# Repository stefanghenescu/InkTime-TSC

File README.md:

# InkTime TSC

## Block Diagram

---

## Bill of Materials (BOM)

| Name | Component Type | Package | Part Number / Value | Qty | JLCPCB Part Link | Datasheet Link |
| :--- | :--- | :--- | :--- | :--- | :--- | :--- |
| **U1** | MCU | AQFN-74 | NRF52840 | 1 | [View Part](https://jlcpcb.com/partdetail/NordicSemicon-NRF52840_QIAAR/C190794) | [View Datasheet](https://resources.ampheo.com/static/datasheets/nordic-semiconductor/nrf52840-qiaa-r-rev2.pdf) |
| **IC1** | LiPo Charger | DSBGA-8 | BQ25180YBGR | 1 | [View Part](https://jlcpcb.com/partdetail/TexasInstruments-BQ25180YBGR/C3682423) | [View Datasheet](https://www.ti.com/lit/ds/symlink/bq25180.pdf?ts=1776583277258) |
| **IC2** | Haptic Driver | DSBGA-9 | DRV2605YZFR | 1 | [View Part](https://jlcpcb.com/partdetail/TexasInstruments-DRV2605YZFR/C81079) | [View Datasheet](https://www.ti.com/lit/ds/symlink/drv2605.pdf) |
| **IC3** | IMU / Accelerometer | LGA-12 | BMA423 | 1 | [View Part](https://jlcpcb.com/partdetail/BoschSensortec-BMA421/C5242966) | [View Datasheet](https://files.pine64.org/doc/datasheet/pinetime/BST-BMA421-FL000.pdf) |
| **IC9** | DC/DC Converter | 15-WL-CSP | RT6160AWSC | 1 | [View Part](https://jlcpcb.com/partdetail/RichtekTech-RT6160AWSC/C7065276) | [View Datasheet](https://www.lcsc.com/datasheet/C7065276.pdf?spm=wm.sxq.inf.ggs___wm.ssy.bg.0.xh&lcsc_vid=RVILV1QAFgMLXlRXRFQPBVVeFgVaXwJQTwdfAlJXFAUxVlNRQVReUlFfQVZbUTsOAxUeFF5JWBYZEEoKFBINSQcJGk4dAgUUFAk%3D) |
| **U3** | Fuel Gauge | TDFN-8 | MAX17048G+T10 | 1 | [View Part](https://jlcpcb.com/partdetail/2777647-MAX17048GT10/C2682616) | [View Datasheet](https://www.analog.com/media/en/technical-documentation/data-sheets/max17048-max17049.pdf) |
| **ANT1** | Chip Antenna | ANTC3216 | 2450AT18B100E | 1 | [View Part](https://jlcpcb.com/partdetail/JohansonDielectrics-2450AT18B100E/C2917717) | [View Datasheet](https://www.johansontechnology.com/docs/1187/2450AT18B100_X8XXogU.pdf) |
| **J1** | FPC Connector | 5034802400 | 503480-2400 | 1 | [View Part](https://jlcpcb.com/partdetail/MOLEX-5034802400/C122434) | [View Datasheet](https://www.mouser.com/datasheet/2/276/2/5034802400_FFC_FPC_CONNECTORS-1112921.pdf?srsltid=AfmBOoqeIvrMEurBUIMiLpCQbdFw00xQXV8qCybaZ2IhZAIdW5Bf1d4q) |
| **J2** | Debug Connector | TC2030IDC | TC2030-IDC | 1 | - | [View Datasheet](https://www.tag-connect.com/wp-content/uploads/bsk-pdf-manager/2019/12/TC2030-IDC-Datasheet-Rev-B.pdf) |
| **J4** | USB-C Connector | KH-TYPE-C-16P | KH-TYPE-C-16P | 1 | [View Part](https://jlcpcb.com/partdetail/Shenzhen_KinghelmElec-KH_TYPE_C16P/C709357) | [View Datasheet](https://www.lcsc.com/datasheet/C709357.pdf) |
| **Q1** | P-Channel MOSFET | SOT23-3 | DMG2305UX-7 | 1 | [View Part](https://jlcpcb.com/partdetail/DiodesIncorporated-DMG2305UX7/C150470) | [View Datasheet](https://www.lcsc.com/datasheet/C150470.pdf?spm=wm.sxq.inf.ggs___wm.ssy.bg.0.xh&lcsc_vid=RVILV1QAFgMLXlRXRFQPBVVeFgVaXwJQTwdfAlJXFAUxVlNRQVReUVxRQFhXUzsOAxUeFF5JWBYZEEoKFBINSQcJGk4dAgUUFAk%3D) |
| **Q3** | N-Channel MOSFET | SC-70 / SOT-323 | SI1308EDL-T1-GE3 | 1 | [View Part](https://jlcpcb.com/partdetail/VishayIntertech-SI1308EDL_T1GE3/C469327) | [View Datasheet](https://www.lcsc.com/datasheet/C469327.pdf?spm=wm.sxq.inf.ggs___wm.ssy.bg.0.xh&lcsc_vid=RVILV1QAFgMLXlRXRFQPBVVeFgVaXwJQTwdfAlJXFAUxVlNRQVReUVBWQ1VdVDsOAxUeFF5JWBYZEEoKFBINSQcJGk4eFQsCAgIaSgADAwAHC0slQFFYUlZRQU8GEwkK) |
| **D2, D4, D5** | Schottky Diode | SOD-123 | MBR0530 | 3 | [View Part](https://jlcpcb.com/partdetail/78464-MBR0530/C77336) | [View Datasheet](https://www.onsemi.com/pdf/datasheet/mbr0530-d.pdf) |
| **D3** | ESD Protection | SOT23-6 | USBLC6-2SC6Y | 1 | [View Part](https://jlcpcb.com/partdetail/STMicroelectronics-USBLC62SC6Y/C2969755) | [View Datasheet](https://www.st.com/resource/en/datasheet/usblc6-2sc6y.pdf) |
| **SW_DN, SW_ENT, SW_UP** | Tactile Button | SMD | EVP-AKE31A | 3 | [View Part](https://jlcpcb.com/partdetail/PANASONIC-EVPAKE31A/C569760) | [View Datasheet](https://docs.rs-online.com/b6df/A700000008633059.pdf) |
| **X1** | Crystal | 2016 | 32MHz | 1 | [View Part](https://jlcpcb.com/partdetail/357115-X201232768KJD2SI/C383843) | [View Datasheet](https://www.lcsc.com/datasheet/C383843.pdf?spm=wm.sxq.inf.ggs___wm.ssy.bg.0.xh&) |lcsc_vid=RVILV1QAFgMLXlRXRFQPBVVeFgVaXwJQTwdfAlJXFAUxVlNRQVReX1FSQlVdUDsOAxUeFF5JWBYZEEoKFBINSQcJGk4eFQsCAgIaSgADAwAHC0slQ1BWUFVTQU8GEwkK |
| **X2** | Crystal | 3215 | 32.768kHz | 1 | [View Part](https://jlcpcb.com/partdetail/YXC_CrystalOscillators-X322532MOB4SI/C9009) | [View Datasheet](https://www.lcsc.com/datasheet/C9009.pdf?spm=wm.sxq.inf.ggs___wm.ssy.bg.0.xh&) |lcsc_vid=RVILV1QAFgMLXlRXRFQPBVVeFgVaXwJQTwdfAlJXFAUxVlNRQVReX1BTRFhZXjsOAxUeFF5JWBYZEEoKFBINSQcJGk4eFQsCAgIaSgADAwAHC0slRlheUF1SWQkaCgg%3D |
| **L1** | Inductor | 0402 | 3.9nH | 1 | [View Part](https://jlcpcb.com/partdetail/MurataElectronics-LQG15HS3N9S02D/C77109) | [View Datasheet](https://static.chipdip.ru/lib/273/DOC012273635.pdf) |
| **L2** | Inductor | 0402 | 10uH | 1 | [View Part](https://jlcpcb.com/partdetail/MurataElectronics-LQW15DN100M00D/C910650) | [View Datasheet](https://www.farnell.com/datasheets/2616941.pdf) |
| **L3** | Inductor | 0402 | 15nH | 1 | [View Part](https://jlcpcb.com/partdetail/MurataElectronics-LQG15HS15NJ02D/C86059) | [View Datasheet](https://eu.mouser.com/datasheet/3/76/3/JELF243B_0010.pdf) |
| **L5** | Inductor | 4828 | 744043680 | 1 | [View Part](https://jlcpcb.com/partdetail/MurataElectronics-LQG15HS27NJ02D/C12669) | [View Datasheet](https://search.murata.co.jp/Ceramy/image/img/P02/JELF243B-0010.pdf) |
| **L7** | Inductor | INDC2016 | FTC252012SR47MBCA | 1 | [View Part](https://jlcpcb.com/partdetail/MurataElectronics-LQW15CNR47K10D/C913544) | [View Datasheet](https://www.mouser.com/datasheet/2/281/1/JELF243A_0096-1380927.pdf?srsltid=AfmBOoqV6fhARUu0Dwcpb8MI3Hh8C0bkpxE3anHGJVMFYBgkCz1oDBQZ) |
| **SJ1** | Solder Jumper | SMD | Jumper | 1 | - | - |
| **R2, R3, R4** | Resistor | 0201 | 0Ω | 3 | [View Part](https://jlcpcb.com/partdetail/YAGEO-RC0201FR070RL/C106227) | [View Datasheet](https://www.mouser.com/catalog/specsheets/YAGEO_PYu_RC_Group_51_RoHS_L_12.pdf?_gl=1*9j379c*_gcl_au*MTAzNzQ1MDU5LjE3NzY2NjMyNjQ.*_ga*NjY5NTI4MTAxLjE3NzY2NjMyNjQ.*_ga_15W4STQT4T*czE3NzY2NjY1ODckbzIkZzEkdDE3NzY2Njc2MjYkajYwJGwwJGgw) |
| **R1_EP_DR** | Resistor | 0201 | 0.47Ω | 1 | [View Part](https://jlcpcb.com/partdetail/21809-25121WF470LT4E/C21097) | [View Datasheet](https://www.royalohm.com/assets/pdf/products/smd/1.pdf) |
| **R_TYPE_SEL** | Resistor | 0201 | 2.2Ω | 1 | [View Part](https://jlcpcb.com/partdetail/YAGEO-RC0201FR072R2L/C138154) | [View Datasheet](https://www.mouser.com/catalog/specsheets/YAGEO_PYu_RC_Group_51_RoHS_L_12.pdf) |
| **R17, R18** | Resistor | 0201 | 3.3kΩ | 2 | [View Part](https://jlcpcb.com/partdetail/YAGEO-AC0201FR073K3L/C226534) | [View Datasheet](https://ro.mouser.com/datasheet/3/508/1/PYU_AC_51_ROHS_L.pdf) |
| **R1_USB, R2_USB** | Resistor | 0201 | 5.1kΩ | 2 | [View Part](https://jlcpcb.com/partdetail/YAGEO-RC0201JR075K1L/C163490) | [View Datasheet](https://yageogroup.com/component-documentation/download/specsheet/RC0201JR-075K1L) |
| **R2_EP_DR, R9, R_PWR_EPD** | Resistor | 0201 | 10kΩ | 3 | [View Part](https://jlcpcb.com/partdetail/TEConnectivity-CPF0201D10KC1/C4187156) | [View Datasheet](https://www.te.com/commerce/DocumentDelivery/DDEController?Action=showdoc&DocId=Data+Sheet%7F1773200%7FM%7Fpdf%7FEnglish%7FENG_DS_1773200_M.pdf) |
| **C3, C4** | Capacitor | 0201 | 1pF | 2 | [View Part](https://jlcpcb.com/partdetail/MurataElectronics-GRM0335C1H1R0BA01D/C85893) | [View Datasheet](https://ro.mouser.com/datasheet/3/76/1/GRM0335C1H1R0BA01-01A.pdf) |
| **C1, C2, C17, C18** | Capacitor | 0201 | 12pF | 4 | [View Part](https://jlcpcb.com/partdetail/MurataElectronics-GRM0335C1H120JA01D/C85890) | [View Datasheet](https://docs.rs-online.com/0636/A700000008615927.pdf) |
| **C11** | Capacitor | 0201 | 100pF | 1 | [View Part](https://jlcpcb.com/partdetail/MurataElectronics-GRM0335C1E101JA01D/C76917) | [View Datasheet](https://docs.rs-online.com/3c16/A700000008615521.pdf) |
| **C9** | Capacitor | 0201 | 820pF | 1 | [View Part](https://jlcpcb.com/partdetail/197002-GRM033R71E821KA01D/C185597) | [View Datasheet](https://docs.rs-online.com/7ce9/A700000008614975.pdf) |
| **C10, C13, C16, C22** | Capacitor | 0201 | 47nF | 4 | [View Part](https://jlcpcb.com/partdetail/MurataElectronics-GRM033R60J473KE19D/C85925) | [View Datasheet](https://datasheet.octopart.com/GRM033R60J473KE19D-Murata-datasheet-44105416.pdf) |
| **C5, C7, C8, C12, C19** | Capacitor | 0201 | 100nF | 5 | [View Part](https://jlcpcb.com/partdetail/MurataElectronics-GRM033R60J104KE19D/C76928) | [View Datasheet](https://search.murata.co.jp/Ceramy/image/img/A01X/G101/ENG/GRM033R60J104KE19-01.pdf) |
| **C23, C27, C29, C30, C31, C32, C34, C37, C38, C42** | Capacitor | 0201 | GRM011R60J152KE01L | 10 | [View Part](https://jlcpcb.com/parts/componentSearch?searchTxt=GRM011R60J152KE01L) | [View Datasheet](https://datasheet.octopart.com/GRM011R60J152KE01L-Murata-datasheet-138731756.pdf) |
| **EPD_C5** | Capacitor | 0201 | 0.1uF/50V | 1 | [View Part](https://jlcpcb.com/partdetail/6103901-500R07W104KV4T_0_1uF50v/C5337557) | [View Datasheet](https://www.mouser.com/catalog/specsheets/johanson_joha-s-a0008490164-1.pdf?_gl=1*1dgyi5u*_gcl_au*MTAzNzQ1MDU5LjE3NzY2NjMyNjQuOTYzMzIyOTQ0LjE3NzY2NzA0NDUuMTc3NjY3MDQ0NQ..*_ga*NjY5NTI4MTAxLjE3NzY2NjMyNjQ.*_ga_15W4STQT4T*czE3NzY2NjY1ODckbzIkZzEkdDE3NzY2NzA0NDgkajQ3JGwwJGgw) |
| **C15** | Capacitor | 0402 | 1.0uF | 1 | [View Part](https://jlcpcb.com/partdetail/MurataElectronics-GRM155R60J105KE19D/C15684) | [View Datasheet](https://datasheet4u.com/pdf/1279553/GRM155R60J105KE19D.pdf) |
| **C6, C14, C20, C21, C43** | Capacitor | 0402 | 4.7uF | 5 | [View Part](https://jlcpcb.com/partdetail/MurataElectronics-GRM155R60J475KE96D/C76995) | [View Datasheet](https://www.lcsc.com/datasheet/C76995.pdf?spm=wm.sxq.inf.ggs___wm.ssy.bg.0.xh&lcsc_vid=RVILV1QAFgMLXlRXRFQPBVVeFgVaXwJQTwdfAlJXFAUxVlNRQVReVFNRR1VbVjsOAxUeFF5JWBYZEEoKFBINSQcJGk4dAgUUFAk%3D) |
| **C2-EP-DR** | Capacitor | 0402 | 4.7uF/25V | 1 | [View Part](https://jlcpcb.com/partdetail/DMBJ-RVT1E4R7M0405_4_7UF25V/C970600) | [View Datasheet](https://www.lcsc.com/datasheet/C2895731.pdf?spm=wm.sxq.inf.ggs___wm.ssy.bg.0.xh&lcsc_vid=RVILV1QAFgMLXlRXRFQPBVVeFgVaXwJQTwdfAlJXFAUxVlNRQVReVFdRRVlcUjsOAxUeFF5JWBYZEEoKFBINSQcJGk4eFQsCAgIaSgADAwAHC0slRVlXUlNVRk8GEwkK) |
| **C1-EP-DR, C24, C39** | Capacitor | 0402 | 10uF | 3 | [View Part](https://jlcpcb.com/partdetail/MurataElectronics-GRM155R60J106ME44D/C76991) | [View Datasheet](https://www.mouser.com/catalog/specsheets/murata_03052018_GRM_Series_1.pdf?_gl=1*8xgmsh*_gcl_au*MTAzNzQ1MDU5LjE3NzY2NjMyNjQuOTYzMzIyOTQ0LjE3NzY2NzA0NDUuMTc3NjY3MDQ0NQ..*_ga*NjY5NTI4MTAxLjE3NzY2NjMyNjQ.*_ga_15W4STQT4T*czE3NzY2NjY1ODckbzIkZzEkdDE3NzY2NzA4NzEkajU5JGwwJGgw) |
| **C25, C33** | Capacitor | 0402 | 22uF | 2 | [View Part](https://jlcpcb.com/partdetail/408393-GRM155R60J226ME11D/C415703) | [View Datasheet](https://ro.mouser.com/datasheet/3/76/2/GRM155R60J226ME11_01A.pdf) |
| **EPD_C1, EPD_C2, EPD_C6–12**| Capacitor | 0402 | 1uF/50V | 9 | [View Part](https://jlcpcb.com/partdetail/25795-0201WMJ0100TCE/C25052) | [View Datasheet](https://www.lcsc.com/datasheet/C25052.pdf?spm=wm.sxq.inf.ggs___wm.ssy.bg.0.xh&lcsc_vid=RVILV1QAFgMLXlRXRFQPBVVeFgVaXwJQTwdfAlJXFAUxVlNRQVReUVVSQFBcUjsOAxUeFF5JWBYZEEoKFBINSQcJGk4eFQsCAgIaSgADAwAHC0slRlNcU1dSWQkaCgg%3D) |
| **TP_3.3V, TP_3V3, TP_BAT_GND, TP_GND, TP_ON, TP_OP, TP_RESET, TP_SCL, TP_SDA, TP_SWDCLK, TP_SWDIO, TP_SWO, TP_VBAT, TP_VREG** | Test Pad | TP20R | Test Pad | 14 | - | - |

---

## Hardware Functionality

This section describes the main hardware subsystems of the InkTime smartwatch, focusing on component choices, overall architecture, and how the design is optimized for low power consumption.

---

### 1. Core Processing & RF

**Microcontroller (MCU):**  
The system is built around the **Nordic nRF52840 (ARM Cortex-M4F)**. It was chosen mainly because it already includes Bluetooth Low Energy (BLE 5.0) and USB support, so no extra external communication chips are needed.

**Clocking System:**  
A dual-crystal setup is used:
- 32 MHz crystal for normal processing and wireless communication  
- 32.768 kHz crystal for the real-time clock (RTC) during low-power sleep modes  

This allows the system to keep accurate time while consuming very little energy when idle.

**Wireless Connectivity:**  
A small 2.4 GHz chip antenna is placed at the edge of the PCB. A matching network is used to improve RF performance and ensure stable BLE communication with a phone or other devices.

---

### 2. Power Management Architecture

The power system is designed to keep energy usage as low as possible while maintaining stable operation.

**Charging & Input:**  
Power is supplied through a USB-C connector, with ESD protection for safety. A **BQ25180 power management IC** handles LiPo charging and automatically switches between USB power and battery operation.

**Voltage Regulation:**  
Since battery voltage changes during discharge, an **RT6160 converter** is used to generate a stable 3.3V rail. This ensures the system works reliably across the entire battery range without brownouts.

**Battery Monitoring:**  
A **MAX17048 fuel gauge** estimates battery level. It reads voltage directly, avoiding the need for a current-sense resistor, which helps reduce power loss and saves space.

---

### 3. Display Subsystem

**E-Paper Panel:**  
The visual output is handled by an e-paper display, selected because it offers very good readability in sunlight and keeps the image without consuming power.

**Power Control:**  
The display requires higher voltages for operation, but it is only powered during refresh cycles. The rest of the time, the MCU completely switches it off using a MOSFET-based power gating circuit. This significantly reduces idle power consumption.

---

### 4. Sensing & User Interaction

**Motion Tracking:**  
A BMA42x IMU is used to detect motion, steps, and general activity. Instead of being read continuously, it can generate interrupt signals that wake the MCU only when movement is detected (for example, wrist movement).

**Haptic Feedback:**  
A DRV2605 haptic driver controls a vibration motor. Rather than generating signals manually, the MCU only triggers predefined vibration patterns stored in the driver.

**Tactile Inputs:**  
Three physical buttons are used for user interaction. They include hardware debounce filtering so that inputs remain stable without needing constant software correction.

---

### 5. Communication Buses

To keep the PCB simple and organized, communication is divided based on speed requirements:

**Shared I2C Bus:**  
Used for low-speed peripherals such as the IMU, fuel gauge, charger IC, and haptic driver. This reduces the number of required MCU pins and keeps routing simple.

**Dedicated SPI Bus:**  
Used only for the e-paper display, since it needs higher data throughput during screen updates. Additional control signals (reset, data/command, busy) are used to manage the display operation.

**Debug Interface:**  
Firmware programming and debugging are handled through a SWD interface, which provides full access without requiring a large permanent header on the PCB.

---

### 6. Power Consumption (Estimation)

The system is mainly optimized for low-power operation, with most components active only for short periods and the MCU spending most of the time in sleep mode.

Typical currents:
- nRF52840 active: ~10–15 mA  
- E-paper refresh (peak): ~20–40 mA (short bursts)  
- IMU: ~0.1 mA  
- Haptic motor: ~50–70 mA (very short pulses)  
- Deep sleep: ~2–5 µA  

With a ~180 mAh LiPo battery and a mostly idle usage pattern (sleep + occasional updates), the estimated battery life is around **5 days**.

---
## nRF52840 Pin Mapping
| Pin | Component / Block | Purpose |
|:--- |:--- |:--- |
| **---** | **Power & Regulation** | **---** |
| **VDD** | MCU Power | Main 3.3V supply for the microcontroller. |
| **VDDH** | MCU Power | High-voltage supply input. |
| **VSS / VSS_PA / VSS_PAD** | Ground | Ground connections for MCU and RF stages. |
| **DEC[1..6] / DEC3V3** | Internal Regulation | Decoupling pins for internal regulators and 3.3V rail stability. |
| **DCC** | DC/DC | Support pins for the internal DC/DC converter. |
| **---** | **Clock & RF** | **---** |
| **XC1 / XC2** | System Clock | 32 MHz crystal oscillator for main operation. |
| **XL1 / XL2** | System Clock | 32.768 kHz crystal for RTC and low-power modes. |
| **ANT** | Antenna | Connection to the 2.4 GHz RF output. |
| **---** | **E-Paper Display (SPI)** | **---** |
| **P0.02** | E-Paper Display | SPI clock (SCK) for display communication. |
| **P0.03** | E-Paper Display | SPI data line (MOSI) for sending pixel data. |
| **P0.05** | E-Paper Display | Chip select to enable the display on the SPI bus. |
| **P0.15** | E-Paper Display | Selects between command and data mode. |
| **P0.16** | E-Paper Display | Hardware reset for the display controller. |
| **P0.17** | E-Paper Display | Busy signal used to synchronize display updates. |
| **P1.01** | E-Paper Display | Controls power gating for the display. |
| **---** | **I2C Bus** | **---** |
| **P0.06** | IMU, Fuel Gauge, Charger, Haptic Driver | Shared I2C data line (SDA) for all peripherals. |
| **P0.07** | IMU, Fuel Gauge, Charger, Haptic Driver | Shared I2C clock line (SCL). |
| **---** | **Sensors & Power ICs** | **---** |
| **P0.08** | IMU | Primary interrupt for motion and wake-up events. |
| **P1.08** | IMU | Secondary interrupt for advanced events. |
| **P0.11** | LiPo Charger | Interrupt line for charge status and fault detection. |
| **P0.10** | Fuel Gauge | Alert signal for low battery or voltage thresholds. |
| **---** | **User Interface** | **---** |
| **P0.12** | Haptic Driver | Enable signal for the vibration motor driver. |
| **P0.13** | Button | User input |
| **P0.14** | Button | User input |
| **P1.02** | Button | User input |
| **---** | **System & SWD** | **---** |
| **P0.18** | System | Global reset line for the microcontroller. |
| **SWDIO** | SWD Interface | Data line for programming and debugging. |
| **SWDCLK** | SWD Interface | Clock line for the debugging interface. |
| **P1.00** | SWD Interface | SWO trace output for advanced debugging. |
| **---** | **USB Interface** | **---** |
| **D+ / D-** | USB Interface | Differential data lines for USB communication. |
| **VBUS** | USB Interface | Used to detect USB connection. |
---
*Note: All other nRF52840 pins not listed in this table are unused.*

## Renders

### PCB Renderings

### Component Placement in Case

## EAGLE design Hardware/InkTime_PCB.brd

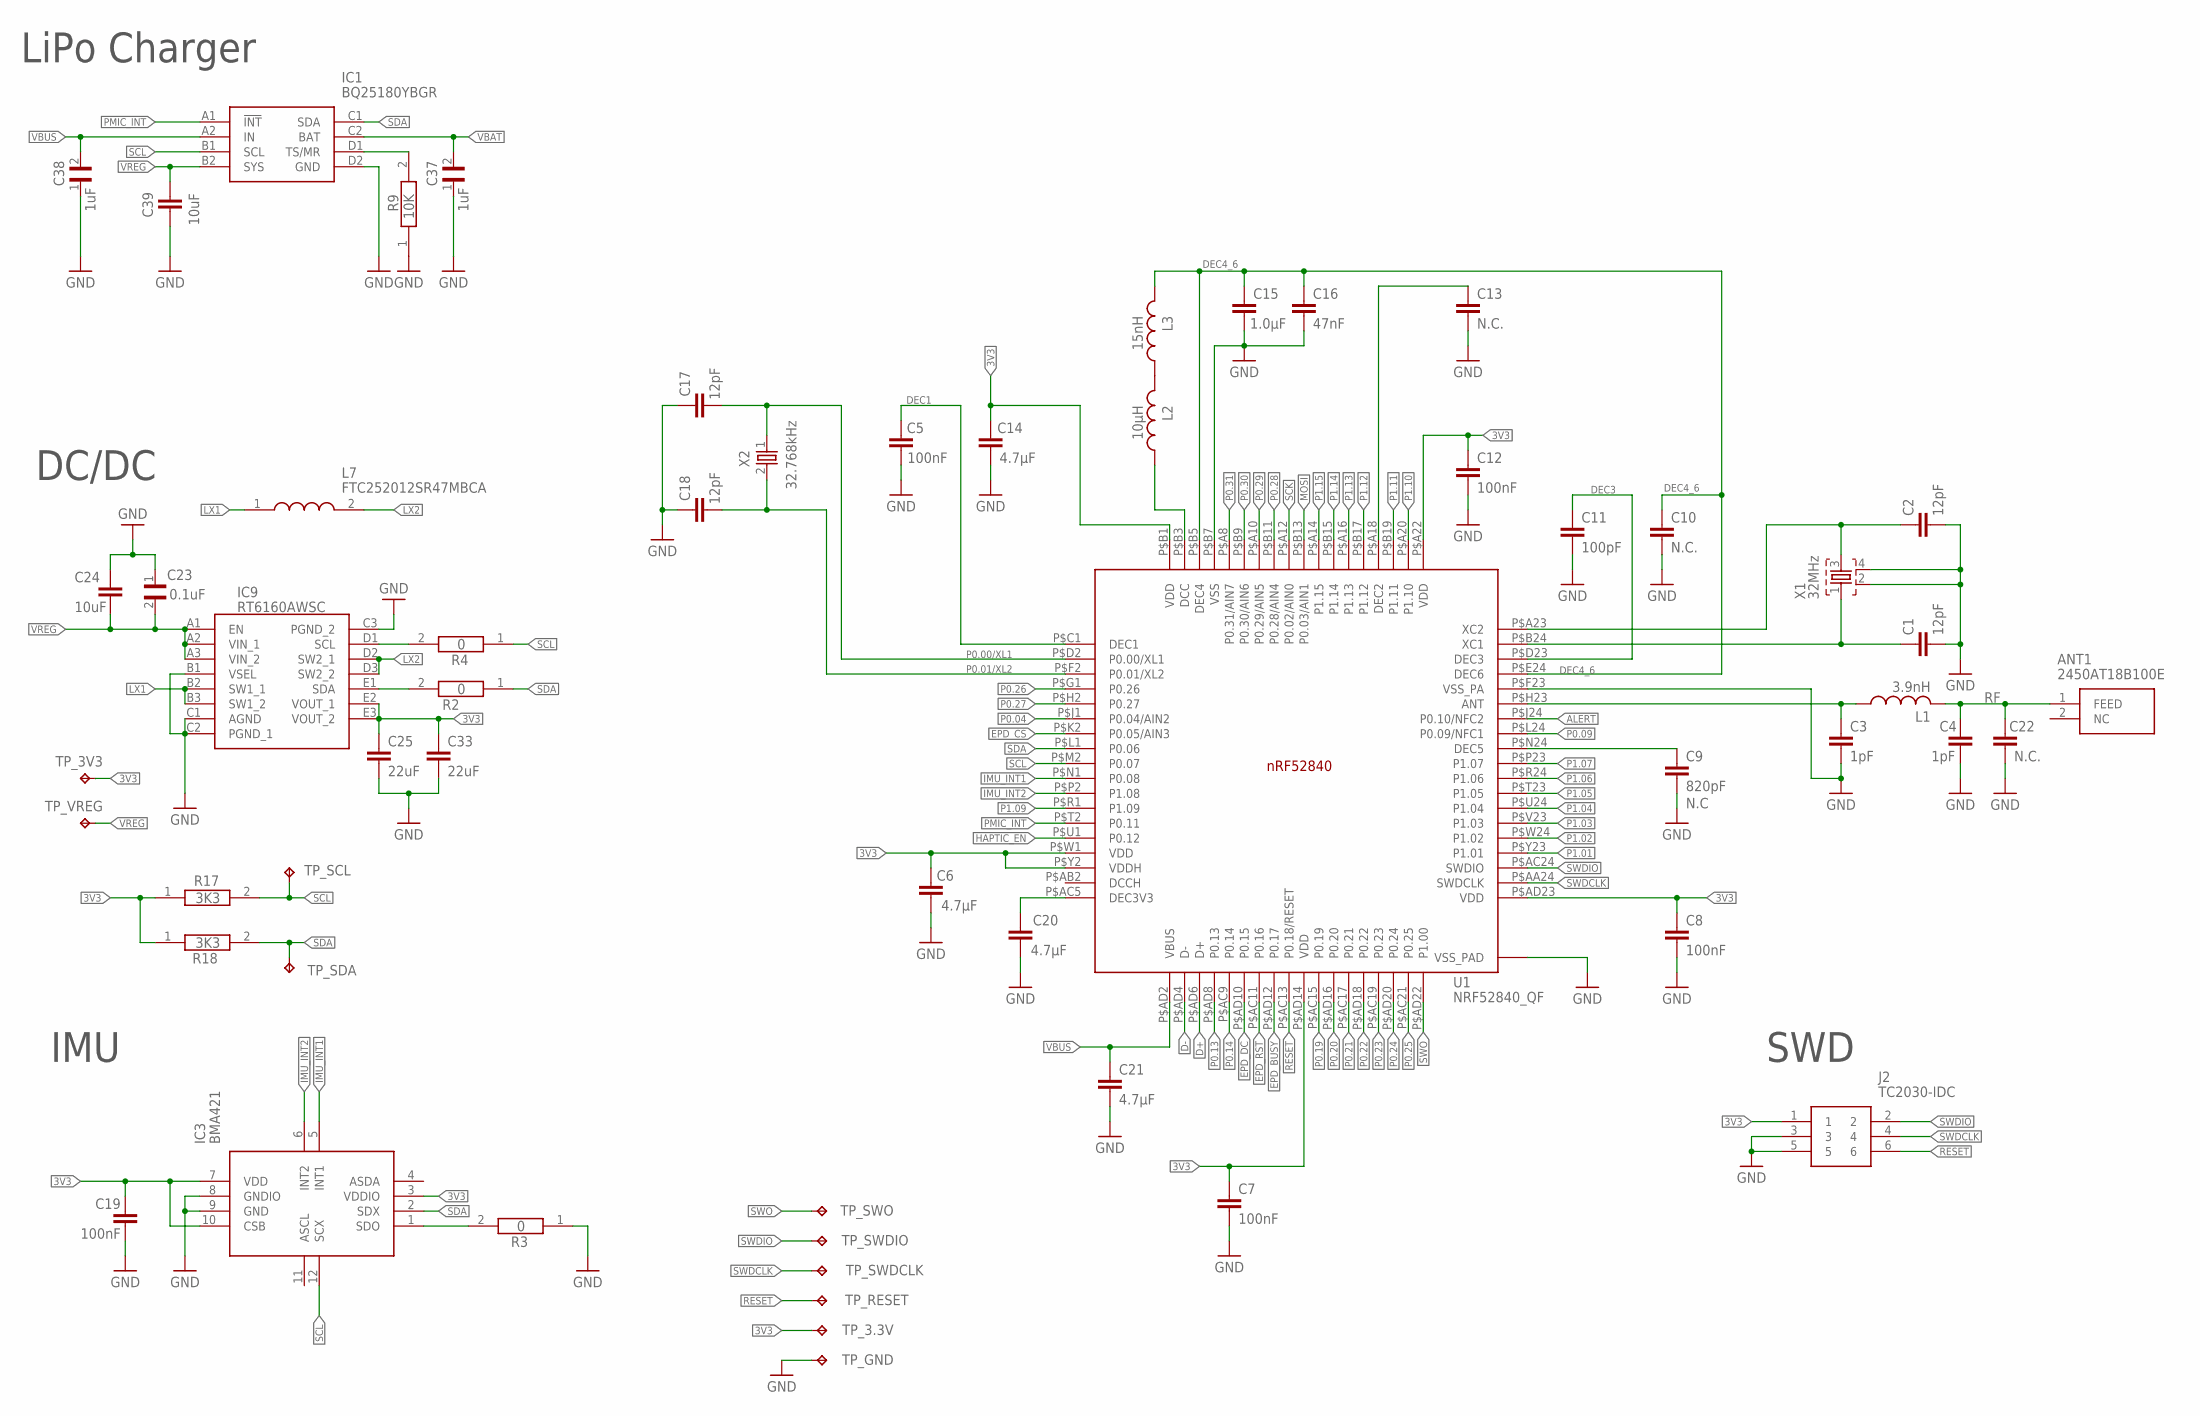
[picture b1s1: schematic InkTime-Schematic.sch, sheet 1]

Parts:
ANT1: 2450AT18B100E; 2450AT18B100E_ANTC3216X140N
C1, C2, C17, C18: 12pF; NORDIC_NRF_3_RESC0201_L
C3, C4: 1pF; NORDIC_NRF_3_RESC0201_L
C5, C7, C8, C12, C19: 100nF; NORDIC_NRF_3_RESC0201_L
C6, C14, C20, C21: 4.7µF; NORDIC_NRF_3_RESC0402_L
C9: 820pF; NORDIC_NRF_3_RESC0201_L
C10, C13, C22: N.C.; NORDIC_NRF_3_RESC0201_L
C11: 100pF; NORDIC_NRF_3_RESC0201_L
C15: 1.0µF; NORDIC_NRF_3_RESC0402_L
C16: 47nF; NORDIC_NRF_3_RESC0201_L
C23: 0.1uF; GRM011R60J152KE01L_1_0201
C24, C39: 10uF; NORDIC_NRF_3_RESC0402_L
C25, C33: 22uF; NORDIC_NRF_3_RESC0402_L
C37, C38: 1uF; GRM011R60J152KE01L_1_0201
IC1: BQ25180YBGR; BQ25180YBGR_BGA8C40P2X4_100X155X50
IC3: BMA421; BMA423_BMA423
IC9: RT6160AWSC; RT6160AWSC_BGA15C40P3X5_140X230X60
J2: TC2030-IDC; TC2030-IDC_TC2030IDC
L1: 3.9nH; NORDIC_NRF_2_RESC0402_L
L2: 10µH; NORDIC_NRF_2_RESC0402_L
L3: 15nH; NORDIC_NRF_2_RESC0402_L
L7: FTC252012SR47MBCA; MLP2016SR47MT0S1_INDC2016X100N
R2, R3, R4: 0; CPF0201D7K68C1_0201
R9: 10K; CPF0201D7K68C1_0201
R17, R18: 3K3; CPF0201D7K68C1_0201
TP_3.3V, TP_3V3: HECTOR_WATCH_1_TPTP20R; HECTOR_WATCH_1_TP20R
TP_GND: HECTOR_WATCH_1_TPTP20R; HECTOR_WATCH_1_TP20R
TP_RESET: HECTOR_WATCH_1_TPTP20R; HECTOR_WATCH_1_TP20R
TP_SCL: HECTOR_WATCH_1_TPTP20R; HECTOR_WATCH_1_TP20R
TP_SDA: HECTOR_WATCH_1_TPTP20R; HECTOR_WATCH_1_TP20R
TP_SWDCLK: HECTOR_WATCH_1_TPTP20R; HECTOR_WATCH_1_TP20R
TP_SWDIO: HECTOR_WATCH_1_TPTP20R; HECTOR_WATCH_1_TP20R
TP_SWO: HECTOR_WATCH_1_TPTP20R; HECTOR_WATCH_1_TP20R
TP_VREG: HECTOR_WATCH_1_TPTP20R; HECTOR_WATCH_1_TP20R
U1: NRF52840_QF; NORDIC_NRF_4_AQFN50P700X700X85_HS-74N
X1: 32MHz; NORDIC_NRF_BT-XTAL_2016_N
X2: 32.768kHz; NORDIC_NRF_1_XTAL_3215_N

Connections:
3V3: C6.2, C7.1, C8.1, C12.1, C14.2, C19.1, C25.1, C33.1, IC3.3 (VDDIO), IC3.7 (VDD), IC3.10 (CSB), IC9.E2 (VOUT_1), IC9.E3 (VOUT_2), J2.1, R17.1, R18.1, TP_3.3V.TP, TP_3V3.TP, U1.P$A22 (VDD), U1.P$AD14 (VDD), U1.P$AD23 (VDD), U1.P$B1 (VDD), U1.P$W1 (VDD), U1.P$Y2 (VDDH); also elsewhere on the board
ALERT: U1.P$J24 (P0.10/NFC2); also elsewhere on the board
D+: U1.P$AD6 (D+); also elsewhere on the board
D-: U1.P$AD4 (D-); also elsewhere on the board
EPD_BUSY: U1.P$AD12 (P0.17); also elsewhere on the board
EPD_CS: U1.P$K2 (P0.05/AIN3); also elsewhere on the board
EPD_DC: U1.P$AD10 (P0.15); also elsewhere on the board
EPD_RST: U1.P$AC11 (P0.16); also elsewhere on the board
GND: C1.2, C2.2, C3.2, C4.2, C5.1, C6.1, C7.2, C8.2, C9.2, C10.2, C11.2, C12.2, C13.2, C14.1, C15.2, C16.2, C17.1, C18.1, C19.2, C20.1, C21.2, C22.2, C23.1, C24.1, C25.2, C33.2, C37.1, C38.1, C39.2, IC1.D2 (GND), IC3.8 (GNDIO), IC3.9 (GND), IC9.B1 (VSEL), IC9.C1 (AGND), IC9.C2 (PGND_1), IC9.C3 (PGND_2), J2.3, J2.5, R3.1, R9.1, TP_GND.TP, U1.P$74 (VSS_PAD), U1.P$75 (VSS_PAD), U1.P$76 (VSS_PAD), U1.P$77 (VSS_PAD), U1.P$78 (VSS_PAD), U1.P$79 (VSS_PAD), U1.P$80 (VSS_PAD), U1.P$81 (VSS_PAD), U1.P$82 (VSS_PAD), U1.P$83 (VSS_PAD), U1.P$84 (VSS_PAD), U1.P$85 (VSS_PAD), U1.P$86 (VSS_PAD), U1.P$87 (VSS_PAD), U1.P$88 (VSS_PAD), U1.P$89 (VSS_PAD), U1.P$90 (VSS_PAD), U1.P$B7 (VSS), U1.P$F23 (VSS_PA), X1.2, X1.4; also elsewhere on the board
HAPTIC_EN: U1.P$U1 (P0.12); also elsewhere on the board
IMU_INT1: IC3.5 (INT1), U1.P$N1 (P0.08)
IMU_INT2: IC3.6 (INT2), U1.P$P2 (P1.08)
LX1: IC9.B2 (SW1_1), IC9.B3 (SW1_2), L7.1
LX2: IC9.D2 (SW2_1), IC9.D3 (SW2_2), L7.2
MOSI: U1.P$B13 (P0.03/AIN1); also elsewhere on the board
unnamed: IC1.D1 (TS/MR), R9.2
unnamed: L2.1, U1.P$B3 (DCC)
unnamed: IC9.D1 (SCL), R4.2
unnamed: IC9.E1 (SDA), R2.2
unnamed: IC3.1 (SDO), R3.2
unnamed: C20.2, U1.P$AC5 (DEC3V3)
unnamed: L2.2, L3.1
unnamed: C13.1, U1.P$A18 (DEC2)
unnamed: C5.2, U1.P$C1 (DEC1)
unnamed: C10.1, C15.1, C16.1, L3.2, U1.P$B5 (DEC4), U1.P$E24 (DEC6)
unnamed: C11.1, U1.P$D23 (DEC3)
unnamed: C17.2, U1.P$D2 (P0.00/XL1), X2.1
unnamed: C18.2, U1.P$F2 (P0.01/XL2), X2.2
unnamed: C9.1, U1.P$N24 (DEC5)
unnamed: C3.1, L1.1, U1.P$H23 (ANT)
unnamed: ANT1.1 (FEED), C4.1, C22.1, L1.2
unnamed: C1.1, U1.P$B24 (XC1), X1.1
unnamed: C2.1, U1.P$A23 (XC2), X1.3
P0.04: U1.P$J1 (P0.04/AIN2)
P0.09: U1.P$L24 (P0.09/NFC1)
P0.13: U1.P$AD8 (P0.13); also elsewhere on the board
P0.14: U1.P$AC9 (P0.14); also elsewhere on the board
P0.19: U1.P$AD16 (P0.20)
P0.20: U1.P$AC15 (P0.19)
P0.21: U1.P$AC17 (P0.21)
P0.22: U1.P$AD18 (P0.22)
P0.23: U1.P$AC19 (P0.23)
P0.24: U1.P$AD20 (P0.24)
P0.25: U1.P$AC21 (P0.25)
P0.26: U1.P$G1 (P0.26)
P0.27: U1.P$H2 (P0.27)
P0.28: U1.P$B11 (P0.28/AIN4)
P0.29: U1.P$A10 (P0.29/AIN5)
P0.30: U1.P$B9 (P0.30/AIN6)
P0.31: U1.P$A8 (P0.31/AIN7)
P1.01: U1.P$Y23 (P1.01); also elsewhere on the board
P1.02: U1.P$W24 (P1.02); also elsewhere on the board
P1.03: U1.P$V23 (P1.03)
P1.04: U1.P$U24 (P1.04)
P1.05: U1.P$T23 (P1.05)
P1.06: U1.P$R24 (P1.06)
P1.07: U1.P$P23 (P1.07)
P1.09: U1.P$R1 (P1.09)
P1.10: U1.P$A20 (P1.10)
P1.11: U1.P$B19 (P1.11)
P1.12: U1.P$B17 (P1.12)
P1.13: U1.P$A16 (P1.13)
P1.14: U1.P$B15 (P1.14)
P1.15: U1.P$A14 (P1.15)
PMIC_INT: IC1.A1 (!INT), U1.P$T2 (P0.11)
RESET: J2.6, TP_RESET.TP, U1.P$AC13 (P0.18/RESET)
SCK: U1.P$A12 (P0.02/AIN0); also elsewhere on the board
SCL: IC1.B1 (SCL), IC3.12 (SCX), R4.1, R17.2, TP_SCL.TP, U1.P$M2 (P0.07); also elsewhere on the board
SDA: IC1.C1 (SDA), IC3.2 (SDX), R2.1, R18.2, TP_SDA.TP, U1.P$L1 (P0.06); also elsewhere on the board
SWDCLK: J2.4, TP_SWDCLK.TP, U1.P$AA24 (SWDCLK)
SWDIO: J2.2, TP_SWDIO.TP, U1.P$AC24 (SWDIO)
SWO: TP_SWO.TP, U1.P$AD22 (P1.00)
VBAT: C37.2, IC1.C2 (BAT); also elsewhere on the board
VBUS: C21.1, C38.2, IC1.A2 (IN), U1.P$AD2 (VBUS); also elsewhere on the board
VREG: C23.2, C24.2, C39.1, IC1.B2 (SYS), IC9.A1 (EN), IC9.A2 (VIN_1), IC9.A3 (VIN_2), TP_VREG.TP

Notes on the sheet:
SWD
LiPo Charger
DC/DC
IMU
N.C
DEC4_6
DEC3
DEC1
P0.00/XL1
P0.01/XL2

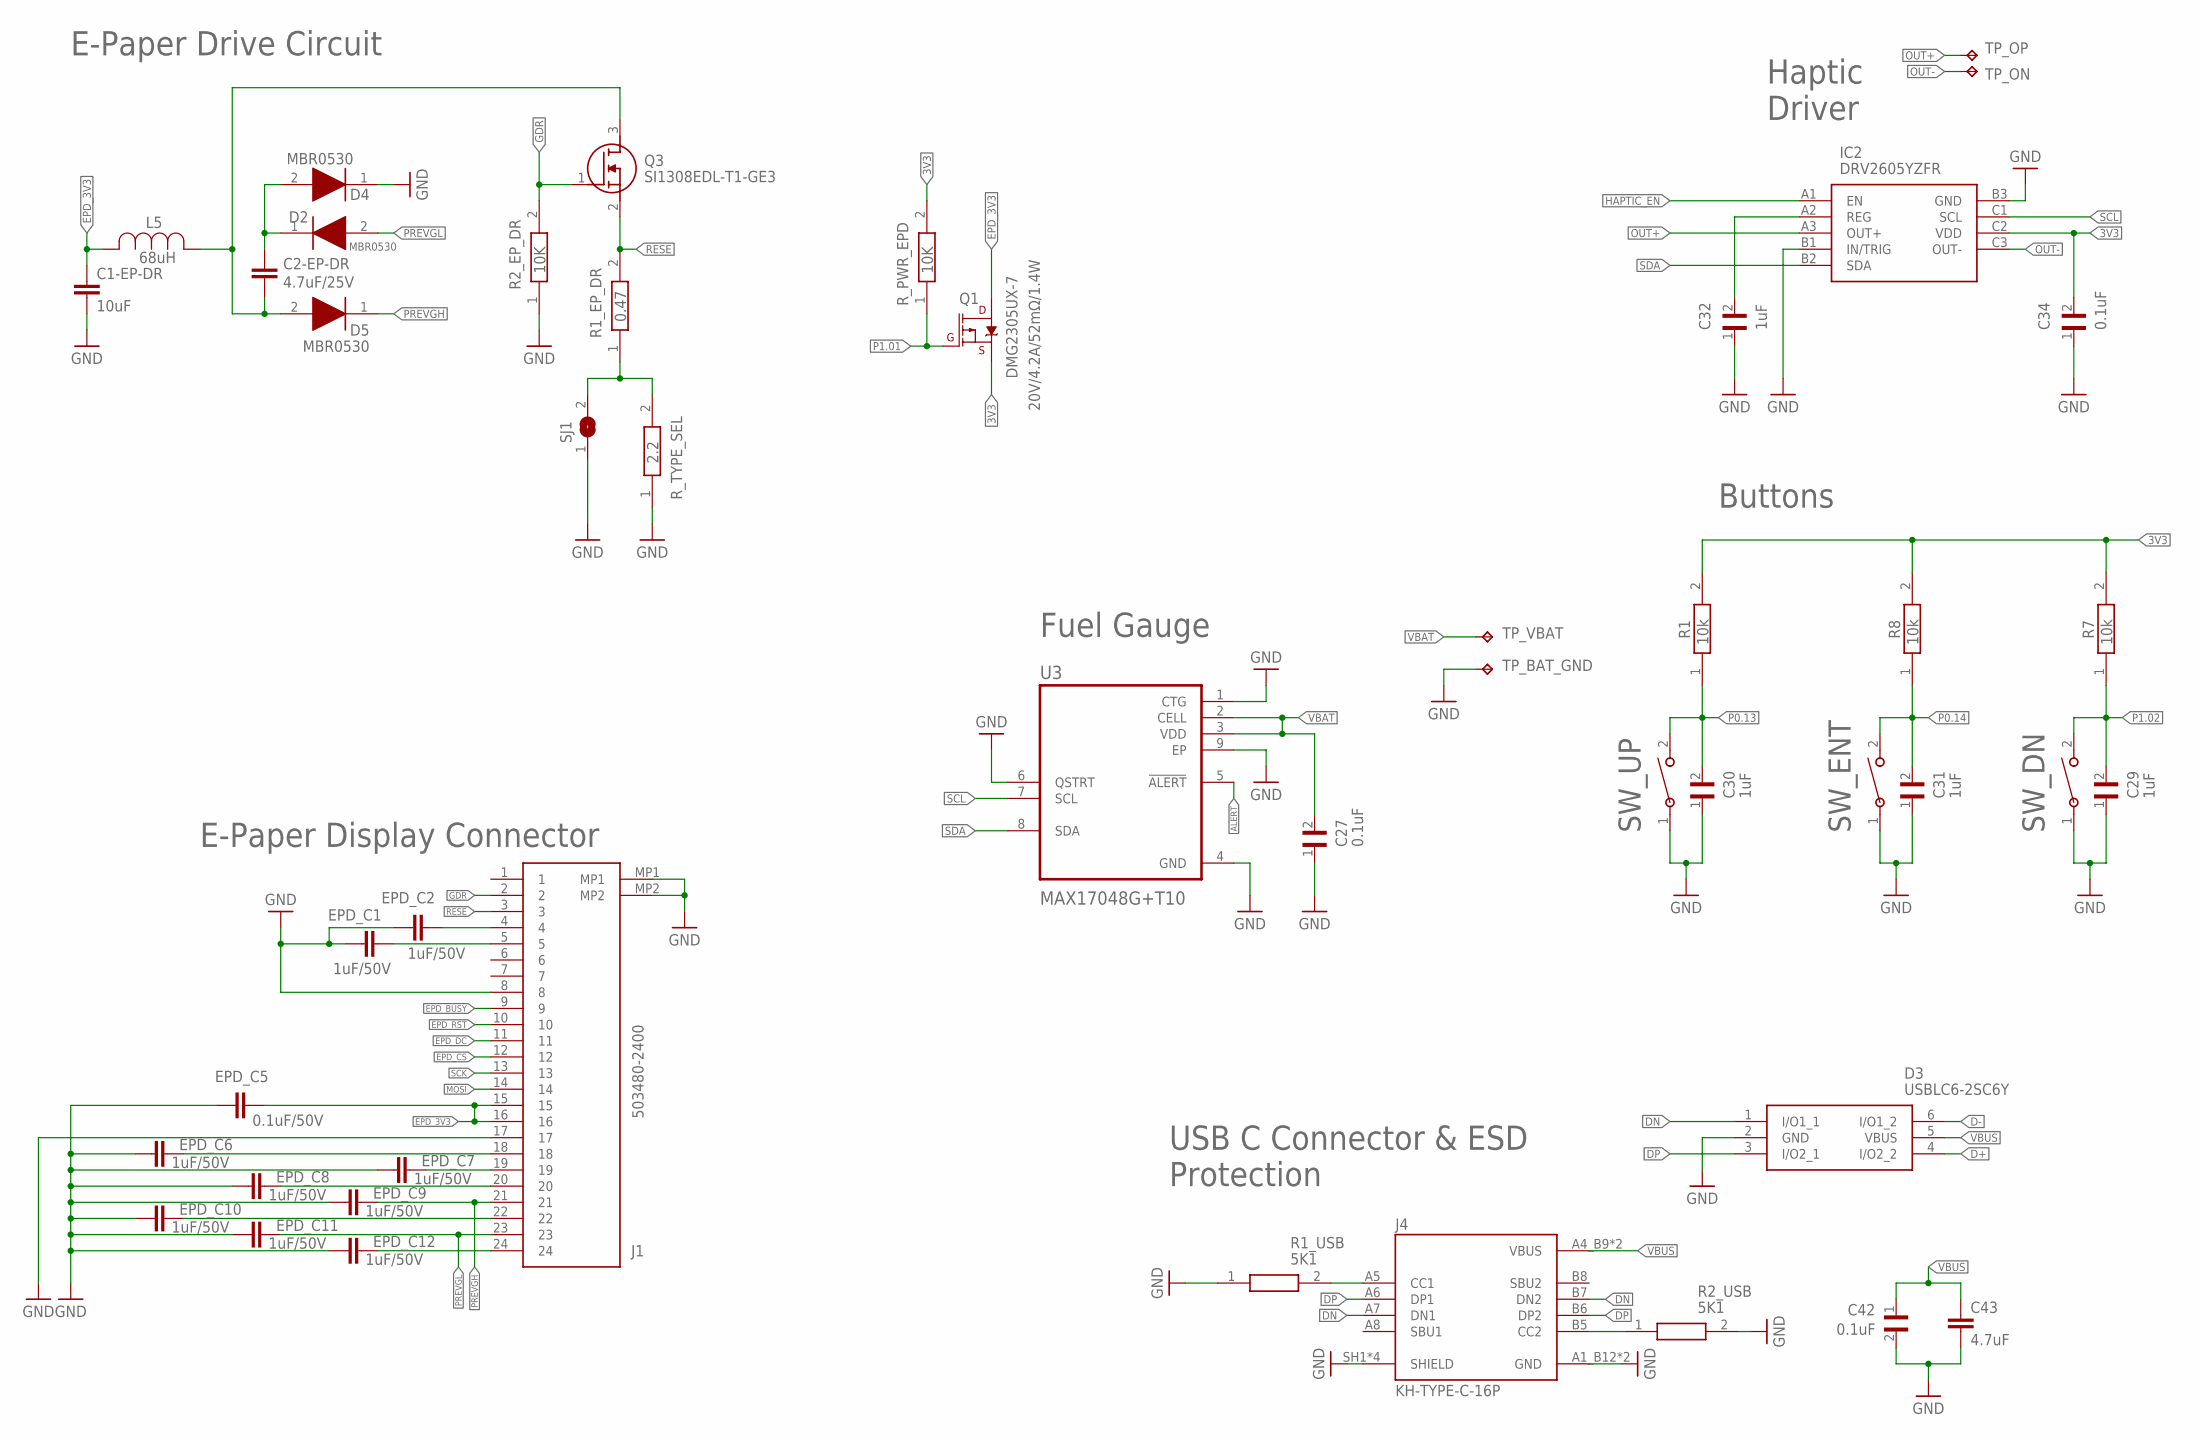
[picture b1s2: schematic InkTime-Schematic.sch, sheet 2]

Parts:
C1-EP-DR: 10uF; NORDIC_NRF_3_RESC0402_L
C2-EP-DR: 4.7uF/25V; NORDIC_NRF_3_RESC0402_L
C27, C34, C42: 0.1uF; GRM011R60J152KE01L_1_0201
C29, C30, C31, C32: 1uF; GRM011R60J152KE01L_1_0201
C43: 4.7uF; NORDIC_NRF_3_RESC0402_L
D2, D4, D5: MBR0530; ESP32_C6_LIBRARY_5_SOD3716X135N
D3: USBLC6-2SC6Y; ESP32_C6_LIBRARY_3_SOT95P280X145-6N
EPD_C1, EPD_C2, EPD_C6, EPD_C7, EPD_C8, EPD_C9, EPD_C10, EPD_C11, EPD_C12: 1uF/50V; NORDIC_NRF_3_RESC0402_L
EPD_C5: 0.1uF/50V; NORDIC_NRF_3_RESC0201_L
IC2: DRV2605YZFR; DRV2605YZFR_BGA9C50P3X3_144X144X62
J1: 503480-2400; 503480-2400_5034802400
J4: KH-TYPE-C-16P; KH-TYPE-C-16P_KINGHELM_KH-TYPE-C-16P
L5: 68uH; ESP32_C6_LIBRARY_2_IND_4828-WE-TPC_WRE
Q1: 20V/4.2A/52mΩ/1.4W; ESP32_C6_LIBRARY_4_ESP32_C6_LIBRARY_4_ESP32_C6_LIBRARY_4_ES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
Q3: SI1308EDL-T1-GE3; ESP32_C6_LIBRARY_6_SOT65P210X110-3N
R1, R7, R8: 10k; CPF0201D7K68C1_0201
R1_EP_DR: 0.47; CPF0201D7K68C1_0201
R1_USB, R2_USB: 5K1; CPF0201D7K68C1_0201
R2_EP_DR: 10K; CPF0201D7K68C1_0201
R_PWR_EPD: 10K; CPF0201D7K68C1_0201
R_TYPE_SEL: 2.2; CPF0201D7K68C1_0201
SJ1: ESP32_C6_LIBRARY_7_JUMPER_SJ
SW_DN: 2025-10-22_07-23-44_LIBRARY_EVP-AKE31ASW_EVP-AKE3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; 2025-10-22_07-23-44_LIBRARY_SW_EVP-AKE31A_PAN
SW_ENT: 2025-10-22_07-23-44_LIBRARY_EVP-AKE31ASW_EVP-AKE3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; 2025-10-22_07-23-44_LIBRARY_SW_EVP-AKE31A_PAN
SW_UP: 2025-10-22_07-23-44_LIBRARY_EVP-AKE31ASW_EVP-AKE3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; 2025-10-22_07-23-44_LIBRARY_SW_EVP-AKE31A_PAN
TP_BAT_GND: HECTOR_WATCH_1_TPTP20R; HECTOR_WATCH_1_TP20R
TP_ON: HECTOR_WATCH_1_TPTP20R; HECTOR_WATCH_1_TP20R
TP_OP: HECTOR_WATCH_1_TPTP20R; HECTOR_WATCH_1_TP20R
TP_VBAT: HECTOR_WATCH_1_TPTP20R; HECTOR_WATCH_1_TP20R
U3: MAX17048G+T10; ESP32_C6_LIBRARY_SON50P200X200X80-9N

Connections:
3V3: C34.2, IC2.C2 (VDD), Q1.2 (S), R1.2, R7.2, R8.2, R_PWR_EPD.2; also elsewhere on the board
ALERT: U3.5 (!ALERT); also elsewhere on the board
D+: D3.4 (I/O2_2); also elsewhere on the board
D-: D3.6 (I/O1_2); also elsewhere on the board
DN: D3.1 (I/O1_1), J4.A7 (DN1), J4.B7 (DN2)
DP: D3.3 (I/O2_1), J4.A6 (DP1), J4.B6 (DP2)
EPD_3V3: C1-EP-DR.1, EPD_C5.2, J1.15, J1.16, L5.2, Q1.3 (D)
EPD_BUSY: J1.9; also elsewhere on the board
EPD_CS: J1.12; also elsewhere on the board
EPD_DC: J1.11; also elsewhere on the board
EPD_RST: J1.10; also elsewhere on the board
GDR: J1.2, Q3.1 (G), R2_EP_DR.2
GND: C1-EP-DR.2, C27.1, C29.1, C30.1, C31.1, C32.1, C34.1, C42.2, C43.2, D3.2 (GND), D4.1 (K), EPD_C1.1, EPD_C2.1, EPD_C5.1, EPD_C6.1, EPD_C7.1, EPD_C8.1, EPD_C9.1, EPD_C10.1, EPD_C11.1, EPD_C12.1, IC2.B1 (IN/TRIG), IC2.B3 (GND), J1.8, J1.17, J1.MP1, J1.MP2, J4.A1_B12 (GND), J4.A12_B1 (GND), J4.SH1 (SHIELD), J4.SH2 (SHIELD), J4.SH3 (SHIELD), J4.SH4 (SHIELD), R1_USB.1, R2_EP_DR.1, R2_USB.2, R_TYPE_SEL.1, SJ1.1, SW_DN.1, SW_ENT.1, SW_UP.1, TP_BAT_GND.TP, U3.1 (CTG), U3.4 (GND), U3.6 (QSTRT), U3.9 (EP); also elsewhere on the board
HAPTIC_EN: IC2.A1 (EN); also elsewhere on the board
MOSI: J1.14; also elsewhere on the board
unnamed: C2-EP-DR.2, D5.2 (A), L5.1, Q3.3 (D)
unnamed: C2-EP-DR.1, D2.1 (K), D4.2 (A)
unnamed: R1_EP_DR.1, R_TYPE_SEL.2, SJ1.2
unnamed: J4.B5 (CC2), R2_USB.1
unnamed: C32.2, IC2.A2 (REG)
unnamed: EPD_C2.2, J1.4
unnamed: EPD_C1.2, J1.5
unnamed: EPD_C6.2, J1.18
unnamed: J4.A5 (CC1), R1_USB.2
unnamed: EPD_C7.2, J1.19
unnamed: EPD_C8.2, J1.20
unnamed: EPD_C10.2, J1.22
unnamed: EPD_C12.2, J1.24
OUT+: IC2.A3 (OUT+), TP_OP.TP
OUT-: IC2.C3 (OUT-), TP_ON.TP
P0.13: C30.2, R1.1, SW_UP.2; also elsewhere on the board
P0.14: C31.2, R8.1, SW_ENT.2; also elsewhere on the board
P1.01: Q1.1 (G), R_PWR_EPD.1; also elsewhere on the board
P1.02: C29.2, R7.1, SW_DN.2; also elsewhere on the board
PREVGH: D5.1 (K), EPD_C9.2, J1.21
PREVGL: D2.2 (A), EPD_C11.2, J1.23
RESE: J1.3, Q3.2 (S), R1_EP_DR.2
SCK: J1.13; also elsewhere on the board
SCL: IC2.C1 (SCL), U3.7 (SCL); also elsewhere on the board
SDA: IC2.B2 (SDA), U3.8 (SDA); also elsewhere on the board
VBAT: C27.2, TP_VBAT.TP, U3.2 (CELL), U3.3 (VDD); also elsewhere on the board
VBUS: C42.1, C43.1, D3.5 (VBUS), J4.A4_B9 (VBUS), J4.A9_B4 (VBUS); also elsewhere on the board

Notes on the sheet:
E-Paper Drive Circuit
DMG2305UX-7
Haptic Driver
Buttons
USB C Connector & ESD Protection
Fuel Gauge
E-Paper Display Connector

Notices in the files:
parts and their libraries:
Library_Project: COPYRIGHT: Copyright (C) 2024 Ultra Librarian. All rights reserved.
Library_Project: COPYRIGHT: Copyright (C) 2025 Ultra Librarian. All rights reserved.
